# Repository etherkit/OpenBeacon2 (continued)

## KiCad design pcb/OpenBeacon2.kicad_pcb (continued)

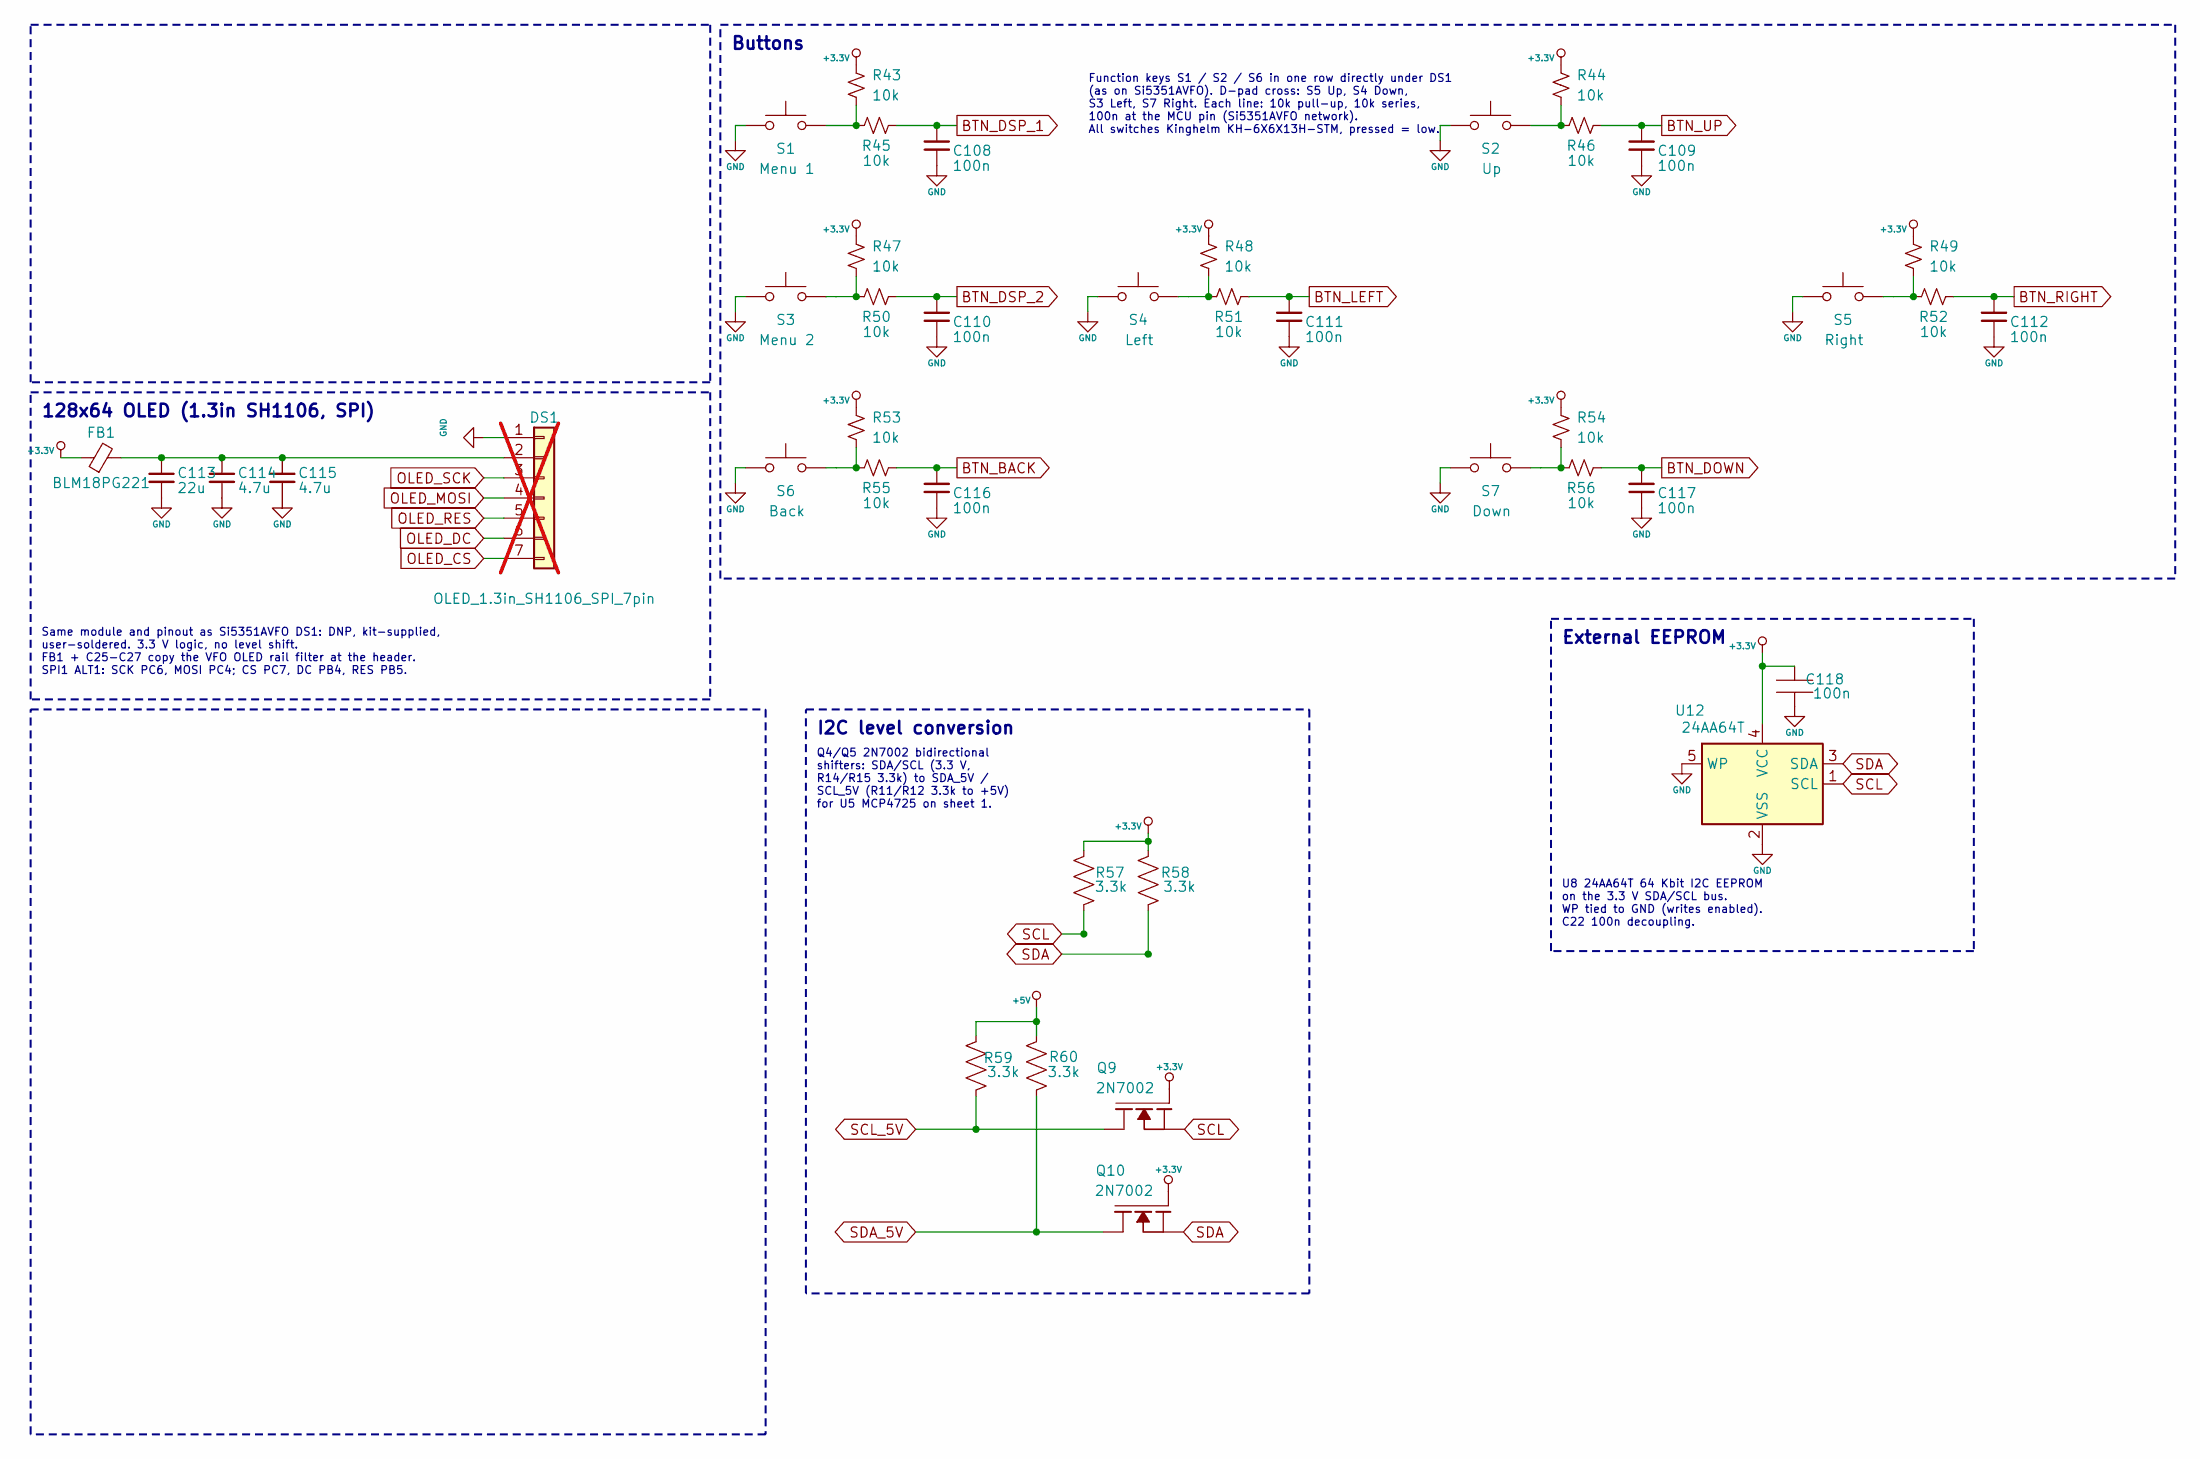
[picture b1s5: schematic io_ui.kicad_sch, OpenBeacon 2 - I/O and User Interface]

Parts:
C108, C109, C110, C111, C112, C116, C117, C118: 100n; C_0805_2012Metric; MPN CC0805KRX7R9BB104; LCSC C49678
C113: 22u; C_1206_3216Metric; MPN CL31A226KAHNNNE; LCSC C12891
C114, C115: 4.7u; C_0805_2012Metric; MPN CL21A475KAQNNNE; LCSC C1779
DS1: OLED_1.3in_SH1106_SPI_7pin; OLED_1.3in_SH1106_PinHeader_1x07_P2.54mm; MPN generic 1.3in SH1106 SPI 7-pin OLED mod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; not fitted
FB1: BLM18PG221; L_0603_1608Metric; MPN BLM18PG221SN1D; LCSC C80165
Q9, Q10: 2N7002; SOT23-2N7002; MPN 2N7002; LCSC C8545
R43, R44, R45, R46, R47, R48, R49, R50, R51, R52, R53, R54, R55, R56: 10k; R_0805_2012Metric; MPN 0805W8F1002T5E; LCSC C17414
R57, R58, R59, R60: 3.3k; R_0805_2012Metric; MPN 0805W8F3301T5E; LCSC C26010
S1: Menu 1; SW_Push_6x6mm_SMD_KH-6X6X13H-STM; MPN KH-6X6X13H-STM; LCSC C2837539
S2: Up; SW_Push_6x6mm_SMD_KH-6X6X13H-STM; MPN KH-6X6X13H-STM; LCSC C2837539
S3: Menu 2; SW_Push_6x6mm_SMD_KH-6X6X13H-STM; MPN KH-6X6X13H-STM; LCSC C2837539
S4: Left; SW_Push_6x6mm_SMD_KH-6X6X13H-STM; MPN KH-6X6X13H-STM; LCSC C2837539
S5: Right; SW_Push_6x6mm_SMD_KH-6X6X13H-STM; MPN KH-6X6X13H-STM; LCSC C2837539
S6: Back; SW_Push_6x6mm_SMD_KH-6X6X13H-STM; MPN KH-6X6X13H-STM; LCSC C2837539
S7: Down; SW_Push_6x6mm_SMD_KH-6X6X13H-STM; MPN KH-6X6X13H-STM; LCSC C2837539
U12: 24AA64T; SOT-23-5; MPN 24AA64T-I/OT; LCSC C2061092

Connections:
+3.3V: C118.1, FB1.1, Q9.2 (G), Q10.2 (G), R43.1, R44.1, R47.1, R48.1, R49.1, R53.1, R54.1, R57.1, R58.1, U12.4 (VCC); also elsewhere on the board
+5V: R59.1, R60.1; also elsewhere on the board
BTN_BACK: C116.1, R55.2; also elsewhere on the board
BTN_DOWN: C117.1, R56.2; also elsewhere on the board
BTN_DSP_1: C108.1, R45.2; also elsewhere on the board
BTN_DSP_2: C110.1, R50.2; also elsewhere on the board
BTN_LEFT: C111.1, R51.2; also elsewhere on the board
BTN_RIGHT: C112.1, R52.2; also elsewhere on the board
BTN_UP: C109.1, R46.2; also elsewhere on the board
GND: C108.2, C109.2, C110.2, C111.2, C112.2, C113.2, C114.2, C115.2, C116.2, C117.2, C118.2, DS1.1, S1.1, S2.1, S3.1, S4.1, S5.1, S6.1, S7.1, U12.2 (VSS), U12.5 (WP); also elsewhere on the board
unnamed: C113.1, C114.1, C115.1, DS1.2, FB1.2
unnamed: R43.2, R45.1, S1.2
unnamed: R44.2, R46.1, S2.2
unnamed: R47.2, R50.1, S3.2
unnamed: R48.2, R51.1, S4.2
unnamed: R49.2, R52.1, S5.2
unnamed: R53.2, R55.1, S6.2
unnamed: R54.2, R56.1, S7.2
OLED_CS: DS1.7; also elsewhere on the board
OLED_DC: DS1.6; also elsewhere on the board
OLED_MOSI: DS1.4; also elsewhere on the board
OLED_RES: DS1.5; also elsewhere on the board
OLED_SCK: DS1.3; also elsewhere on the board
SCL: Q9.1 (S), R57.2, U12.1 (SCL); also elsewhere on the board
SCL_5V: Q9.3 (D), R59.2; also elsewhere on the board
SDA: Q10.1 (S), R58.2, U12.3 (SDA); also elsewhere on the board
SDA_5V: Q10.3 (D), R60.2; also elsewhere on the board

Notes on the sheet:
128x64 OLED (1.3in SH1106, SPI)
Same module and pinout as Si5351AVFO DS1: DNP, kit-supplied, user-soldered. 3.3 V logic, no level shift. FB1 + C25-C27 copy the VFO OLED rail filter at the header. SPI1 ALT1: SCK PC6, MOSI PC4; CS PC7, DC PB4, RES PB5.
Buttons
Function keys S1 / S2 / S6 in one row directly under DS1 (as on Si5351AVFO). D-pad cross: S5 Up, S4 Down, S3 Left, S7 Right. Each line: 10k pull-up, 10k series, 100n at the MCU pin (Si5351AVFO network). All switches Kinghelm KH-6X6X13H-STM, pressed = low.
I2C level conversion
Q4/Q5 2N7002 bidirectional shifters: SDA/SCL (3.3 V, R14/R15 3.3k) to SDA_5V / SCL_5V (R11/R12 3.3k to +5V) for U5 MCP4725 on sheet 1.
External EEPROM
U8 24AA64T 64 Kbit I2C EEPROM on the 3.3 V SDA/SCL bus. WP tied to GND (writes enabled). C22 100n decoupling.

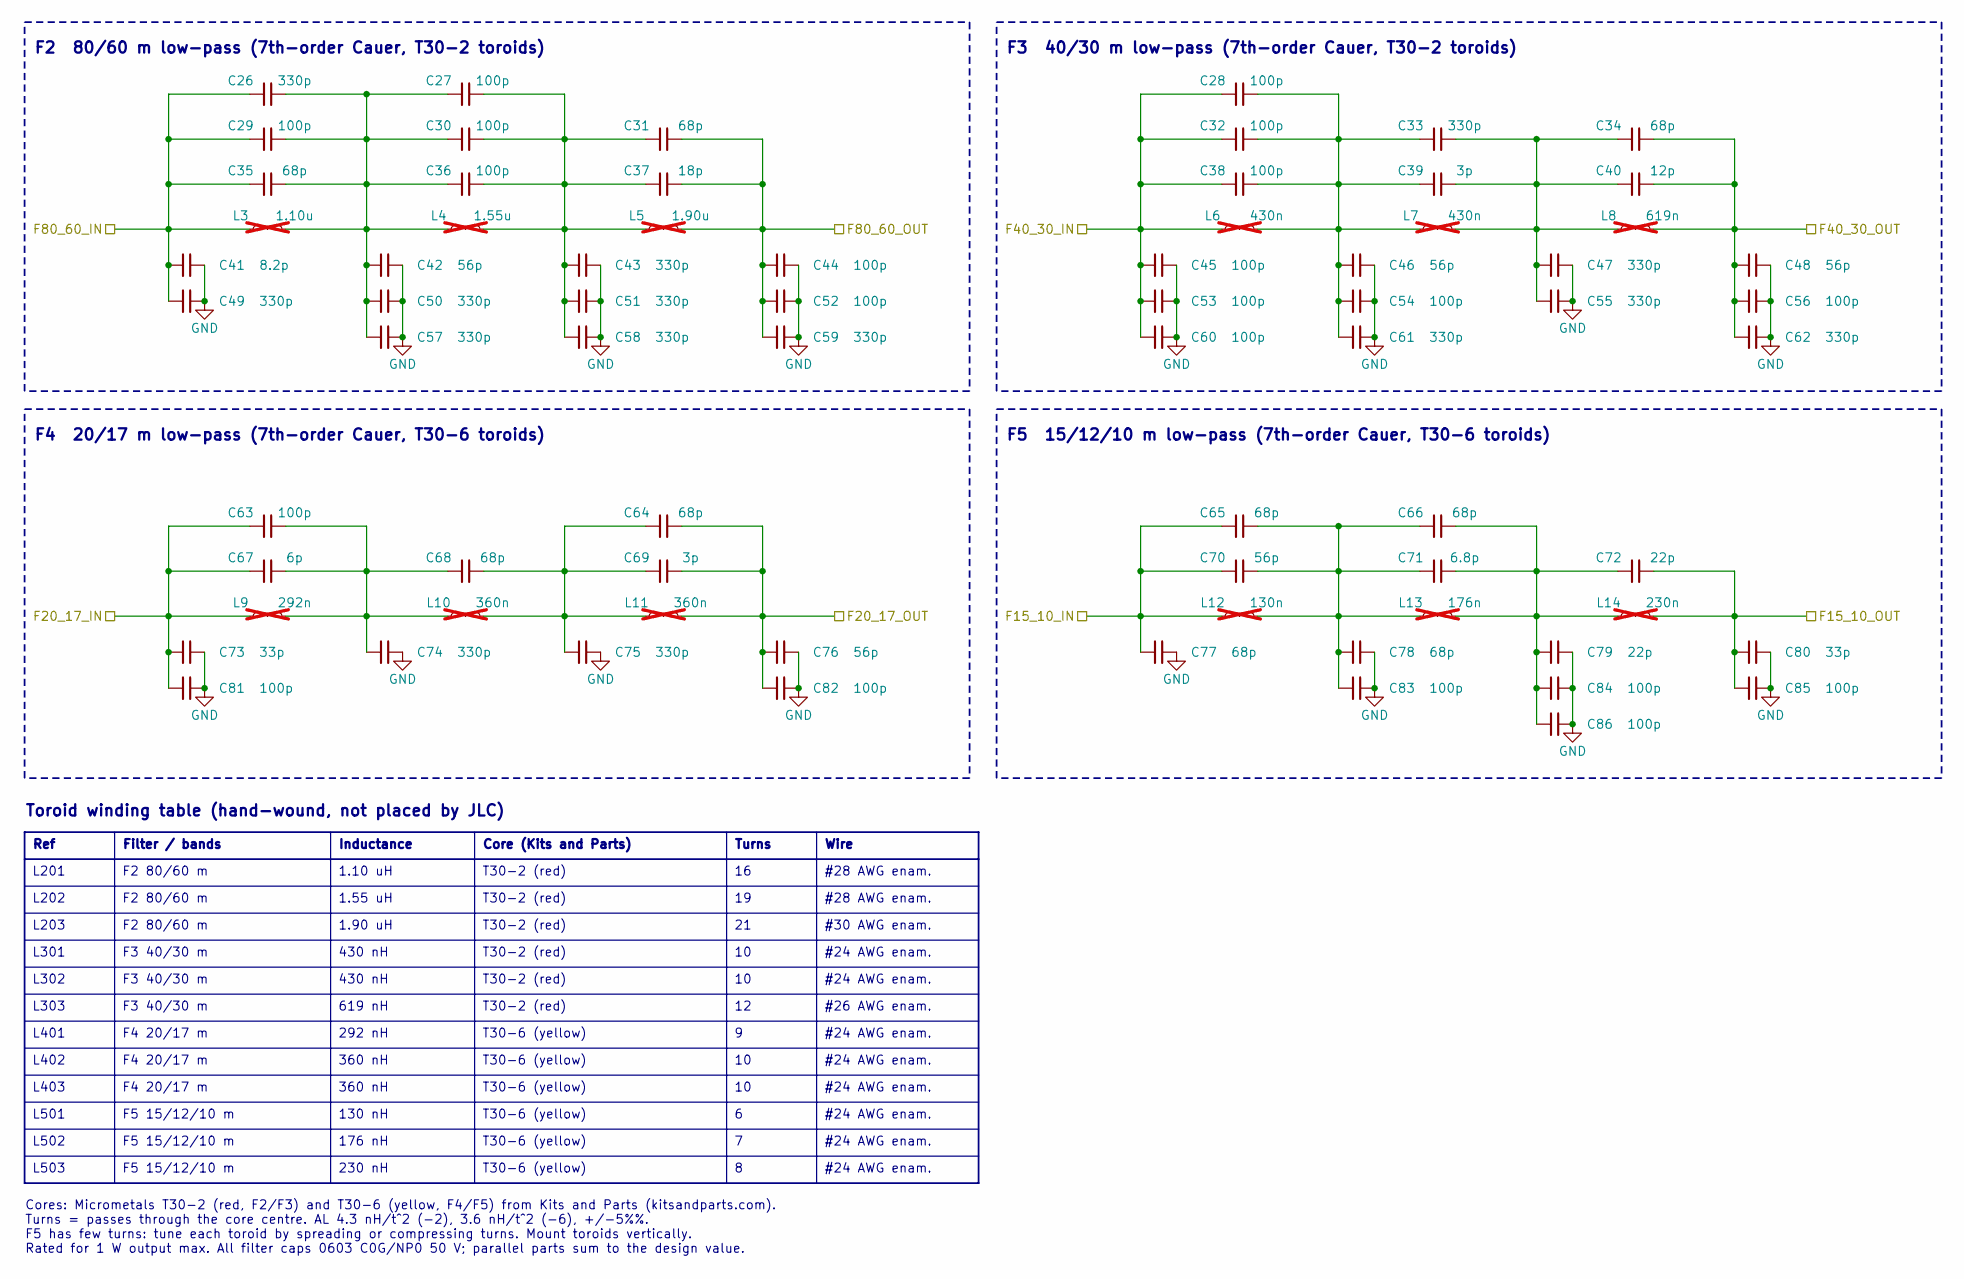
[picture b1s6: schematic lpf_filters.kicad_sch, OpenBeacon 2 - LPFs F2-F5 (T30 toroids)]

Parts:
C26: 330p; C_0603_1608Metric; MPN CC0603JRNPO0BN331; LCSC C327088
C27, C29, C30, C36: 100p; C_0603_1608Metric; MPN CC0603JRNPO0BN101; LCSC C107033
C28, C32, C38, C44, C45, C52, C53, C54, C56, C60, C63, C81, C82, C83, C84, C85, C86: 100p; C_0603_1608Metric; MPN CL10C101JB8NNNC; LCSC C14858
C31, C34, C64, C65, C66, C68, C77, C78: 68p; C_0603_1608Metric; MPN CL10C680JB8NNNC; LCSC C28262
C33, C43, C47, C49, C50, C51, C55, C57, C58, C59, C61, C62, C74, C75: 330p; C_0603_1608Metric; MPN CL10C331JB8NNNC; LCSC C1664
C35: 68p; C_0603_1608Metric; MPN CC0603JRNPO0BN680; LCSC C527065
C37: 18p; C_0603_1608Metric; MPN CL10C180JB8NNNC; LCSC C1647
C39, C69: 3p; C_0603_1608Metric; MPN 0603CG3R0C500NT; LCSC C46219
C40: 12p; C_0603_1608Metric; MPN CL10C120JB8NNNC; LCSC C38523
C41: 8.2p; C_0603_1608Metric; MPN 0603CG8R2C500NT; LCSC C1685
C42, C46, C48, C70, C76: 56p; C_0603_1608Metric; MPN CL10C560JB8NNNC; LCSC C39148
C67: 6p; C_0603_1608Metric; MPN 0603CG6R0C500NT; LCSC C37474
C71: 6.8p; C_0603_1608Metric; MPN 0603CG6R8C500NT; LCSC C1679
C72, C79: 22p; C_0603_1608Metric; MPN CL10C220JB8NNNC; LCSC C1653
C73, C80: 33p; C_0603_1608Metric; MPN CL10C330JB8NNNC; LCSC C1663
L3: 1.10u; L_Toroid_Vertical_L10.0mm_W5.0mm_P5.08mm; MPN T30-2; not fitted
L4: 1.55u; L_Toroid_Vertical_L10.0mm_W5.0mm_P5.08mm; MPN T30-2; not fitted
L5: 1.90u; L_Toroid_Vertical_L10.0mm_W5.0mm_P5.08mm; MPN T30-2; not fitted
L6, L7: 430n; L_Toroid_Vertical_L10.0mm_W5.0mm_P5.08mm; MPN T30-2; not fitted
L8: 619n; L_Toroid_Vertical_L10.0mm_W5.0mm_P5.08mm; MPN T30-2; not fitted
L9: 292n; L_Toroid_Vertical_L10.0mm_W5.0mm_P5.08mm; MPN T30-6; not fitted
L10, L11: 360n; L_Toroid_Vertical_L10.0mm_W5.0mm_P5.08mm; MPN T30-6; not fitted
L12: 130n; L_Toroid_Vertical_L10.0mm_W5.0mm_P5.08mm; MPN T30-6; not fitted
L13: 176n; L_Toroid_Vertical_L10.0mm_W5.0mm_P5.08mm; MPN T30-6; not fitted
L14: 230n; L_Toroid_Vertical_L10.0mm_W5.0mm_P5.08mm; MPN T30-6; not fitted

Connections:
/Filter Bank/F15_10_IN: C65.1, C70.1, C77.1, L12.1; also elsewhere on the board
/Filter Bank/F15_10_OUT: C72.2, C80.1, C85.1, L14.2; also elsewhere on the board
/Filter Bank/F20_17_IN: C63.1, C67.1, C73.1, C81.1, L9.1; also elsewhere on the board
/Filter Bank/F20_17_OUT: C64.2, C69.2, C76.1, C82.1, L11.2; also elsewhere on the board
/Filter Bank/F40_30_IN: C28.1, C32.1, C38.1, C45.1, C53.1, C60.1, L6.1; also elsewhere on the board
/Filter Bank/F40_30_OUT: C34.2, C40.2, C48.1, C56.1, C62.1, L8.2; also elsewhere on the board
/Filter Bank/F80_60_IN: C26.1, C29.1, C35.1, C41.1, C49.1, L3.1; also elsewhere on the board
/Filter Bank/F80_60_OUT: C31.2, C37.2, C44.1, C52.1, C59.1, L5.2; also elsewhere on the board
GND: C41.2, C42.2, C43.2, C44.2, C45.2, C46.2, C47.2, C48.2, C49.2, C50.2, C51.2, C52.2, C53.2, C54.2, C55.2, C56.2, C57.2, C58.2, C59.2, C60.2, C61.2, C62.2, C73.2, C74.2, C75.2, C76.2, C77.2, C78.2, C79.2, C80.2, C81.2, C82.2, C83.2, C84.2, C85.2, C86.2; also elsewhere on the board
unnamed: C26.2, C27.1, C29.2, C30.1, C35.2, C36.1, C42.1, C50.1, C57.1, L3.2, L4.1
unnamed: C27.2, C30.2, C31.1, C36.2, C37.1, C43.1, C51.1, C58.1, L4.2, L5.1
unnamed: C28.2, C32.2, C33.1, C38.2, C39.1, C46.1, C54.1, C61.1, L6.2, L7.1
unnamed: C33.2, C34.1, C39.2, C40.1, C47.1, C55.1, L7.2, L8.1
unnamed: C63.2, C67.2, C68.1, C74.1, L9.2, L10.1
unnamed: C64.1, C68.2, C69.1, C75.1, L10.2, L11.1
unnamed: C65.2, C66.1, C70.2, C71.1, C78.1, C83.1, L12.2, L13.1
unnamed: C66.2, C71.2, C72.1, C79.1, C84.1, C86.1, L13.2, L14.1

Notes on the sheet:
F2 80/60 m low-pass (7th-order Cauer, T30-2 toroids)
F3 40/30 m low-pass (7th-order Cauer, T30-2 toroids)
F4 20/17 m low-pass (7th-order Cauer, T30-6 toroids)
F5 15/12/10 m low-pass (7th-order Cauer, T30-6 toroids)
Toroid winding table (hand-wound, not placed by JLC)
Ref
Filter / bands
Inductance
Core (Kits and Parts)
Turns
Wire
L201
F2 80/60 m
1.10 uH
T30-2 (red)
#28 AWG enam.
L202
1.55 uH
L203
1.90 uH
#30 AWG enam.
L301
F3 40/30 m
430 nH
#24 AWG enam.
L302
L303
619 nH
#26 AWG enam.
L401
F4 20/17 m
292 nH
T30-6 (yellow)
L402
360 nH
L403
L501
F5 15/12/10 m
130 nH
L502

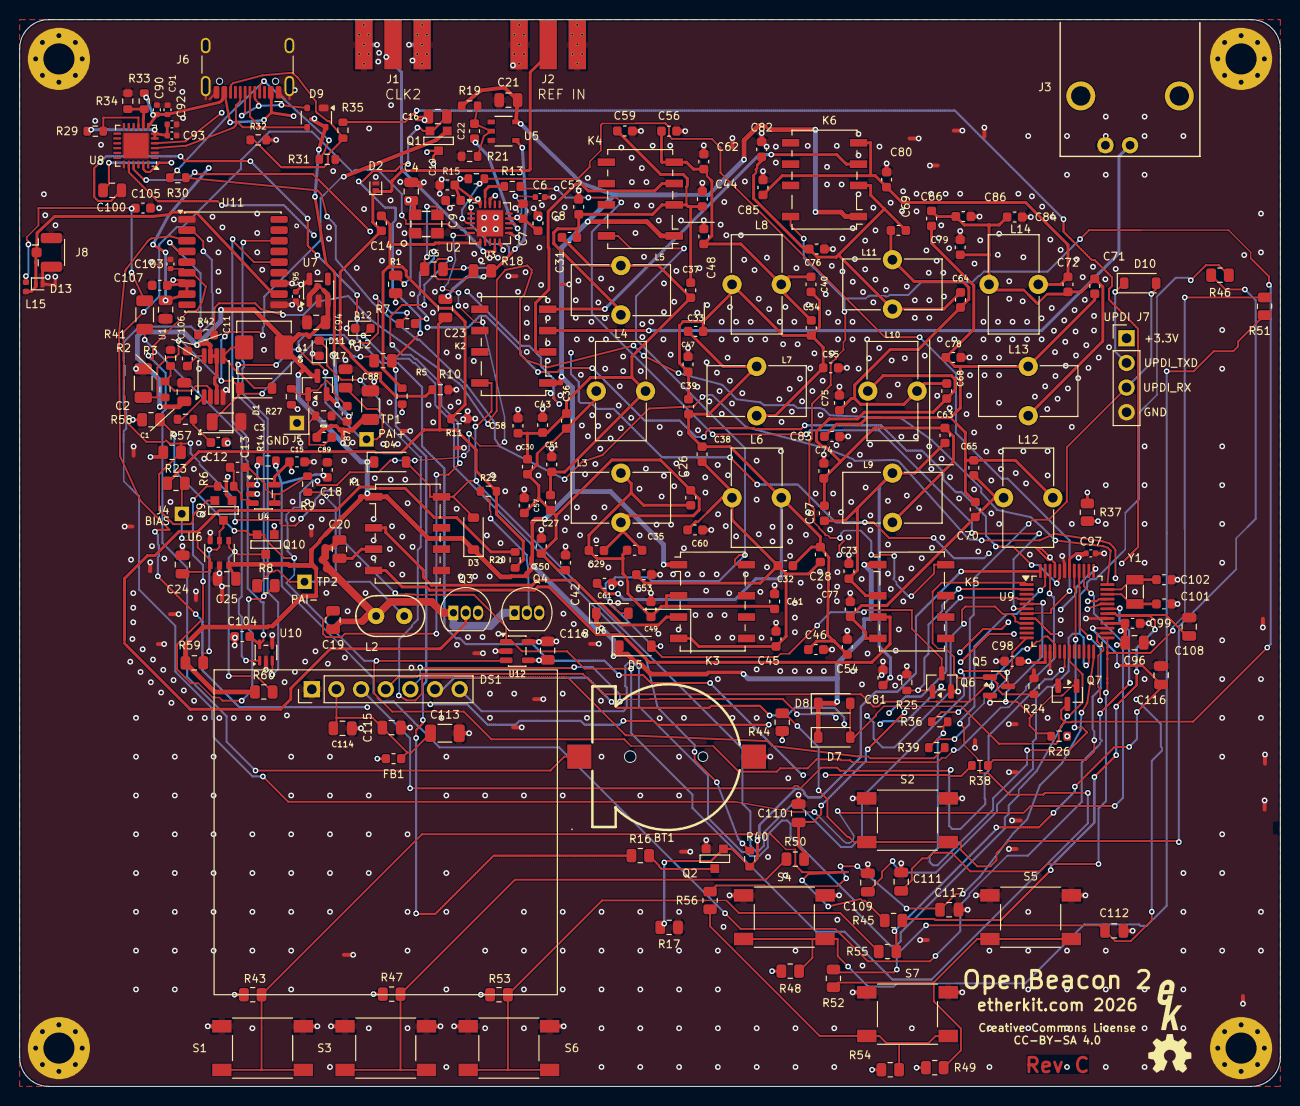
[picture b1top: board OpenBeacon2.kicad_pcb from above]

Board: 4 copper layers, 130.0 x 110.0 mm, 261 parts (0 on the bottom side), 123 nets.

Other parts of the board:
H1, H2, H3, H4: MountingHole_M3; MountingHole_3.2mm_M3_Pad_Via
LOGO1: LOGO; EtherkitLogoSmall
LOGO2: LOGO; OSHWLogo4mm

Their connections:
GND: H1.1, H2.1, H3.1, H4.1; also elsewhere on the board

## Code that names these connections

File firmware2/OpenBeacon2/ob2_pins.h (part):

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 *
 * Transcribed from the firmware spec draft 3.5 (approved), section 2.1,
 * with the section 2.2 power-rework net changes applied. DxCore numbers are
 * the 48pin-standard map (PA0 = 0 ... PF5 = 39). This header includes no
 * Arduino headers, so host tests can compile it.
 *
 * POWER REWORK HARDWARE IS NOT COMMITTED IN THIS REPOSITORY.
 * origin/pcb-layout commit 88e9a62 still has PB1 no-connect and PE1-PE3 on
 * header J5 (labels D31_A9_PE1, D32_A10_PE2, D33_A11_PE3). Spec section 2.2
 * (decision D17) supersedes those four nets. This header follows section 2.2.
 * It is not evidence that the rework schematic has landed.
 *
 * Spec section 2.1 leaves the DxCore column blank for PF0, PF1, RESET/PF6,
 * and UPDI. DxCore still numbers PIN_PF0 = 34, PIN_PF1 = 35, and PIN_PF6 = 40.
 * Those pins are not given firmware GPIO constants here (crystal and reset).
 *
 * The three J5 spares are one row in the spec ("PD0-PD2 / J5"). They are
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
constexpr char OB2_POWER_REWORK_NOTE[] =
    "Power rework (D17) is not committed in this repository. "
    "PB1 BAND_C, PE1 TX_ISENSE, PE2 CC1_SENSE, and PE3 CC2_SENSE follow "
    "spec section 2.2, which supersedes pcb-layout 88e9a62 "
    "(PB1 NC, PE1-PE3 on J5).";

constexpr uint8_t OB2_PIN_REWORK = 1u << 0;
constexpr uint8_t OB2_PIN_OUT = 1u << 1;
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constexpr uint8_t OB2_PIN_NO_GPIO = 1u << 6;

/* Firmware GPIO numbers. Spec section 2.1 "DxCore" column. */
constexpr uint8_t OB2_BAND_A = 5;      /* PA5 */
constexpr uint8_t OB2_BAND_B = 6;      /* PA6 */
constexpr uint8_t OB2_J4_PA7 = 7;      /* PA7, spare J4.1 */
constexpr uint8_t OB2_GPS_RXD = 8;     /* PB0, USART3 TX to the GPS */
constexpr uint8_t OB2_BAND_C = 9;      /* PB1, rework */
constexpr uint8_t OB2_CAL_CLK = 10;    /* PB2, Si5351C CLK4 */
constexpr uint8_t OB2_SI_INTR = 11;    /* PB3 */
constexpr uint8_t OB2_OLED_DC = 12;    /* PB4 */
constexpr uint8_t OB2_OLED_RES = 13;   /* PB5 */
constexpr uint8_t OB2_UART_TX = 14;    /* PC0, USART1 TX, J10 */
constexpr uint8_t OB2_UART_RX = 15;    /* PC1, USART1 RX, J10 */
constexpr uint8_t OB2_SYNC_LED = 16;   /* PC2 */
constexpr uint8_t OB2_J4_PC3 = 17;     /* PC3, spare J4.3 */
constexpr uint8_t OB2_OLED_MOSI = 18;  /* PC4, SPI1 ALT1 */
constexpr uint8_t OB2_J4_PC5 = 19;     /* PC5, spare J4.5, SPI1 ALT1 MISO */
constexpr uint8_t OB2_OLED_SCK = 20;   /* PC6, SPI1 ALT1 */
constexpr uint8_t OB2_OLED_CS = 21;    /* PC7, SPI1 ALT1 SS as GPIO */
constexpr uint8_t OB2_J5_PD0 = 22;     /* PD0, spare ADC A0 */
constexpr uint8_t OB2_J5_PD1 = 23;     /* PD1, spare ADC A1 */
constexpr uint8_t OB2_J5_PD2 = 24;     /* PD2, spare ADC A2 */
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constexpr uint8_t OB2_BTN_DOWN = 26;
constexpr uint8_t OB2_BTN_LEFT = 27;
constexpr uint8_t OB2_BTN_RIGHT = 28;
constexpr uint8_t OB2_BTN_BACK = 29;   /* PD7. Do not select VREFA. */
constexpr uint8_t OB2_BTN_DSP_1 = 30;  /* PE0 */
constexpr uint8_t OB2_TX_ISENSE = 31;  /* PE1, AIN9, rework */
constexpr uint8_t OB2_CC1_SENSE = 32;  /* PE2, AIN10, rework */
constexpr uint8_t OB2_CC2_SENSE = 33;  /* PE3, AIN11, rework */
constexpr uint8_t OB2_GPS_PPS = 36;    /* PF2 */
constexpr uint8_t OB2_BTN_DSP_2 = 37;  /* PF3 */
constexpr uint8_t OB2_J4_PF4 = 38;     /* PF4, spare J4.7 */
constexpr uint8_t OB2_GPS_TXD = 39;    /* PF5, USART2 RX ALT1 */
constexpr uint8_t OB2_MCU_TX = 0;      /* PA0, USART0 TX to the CP2102N */
constexpr uint8_t OB2_MCU_RX = 1;      /* PA1, USART0 RX */
constexpr uint8_t OB2_SDA = 2;         /* PA2, TWI0 */
constexpr uint8_t OB2_SCL = 3;         /* PA3, TWI0 */
constexpr uint8_t OB2_TX = 4;          /* PA4, 12 V PA supply and TX LED */

constexpr int8_t OB2_AIN_J5_PD0 = 0;
constexpr int8_t OB2_AIN_J5_PD1 = 1;
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constexpr int8_t OB2_AIN_CC2_SENSE = 11;

/*
 * USART2 on ALT1, RX only: GPS TXD -> PF5. ALT1 TX is PF4 (J4.7) and must
 * stay a GPIO. Default USART2 would sit on the 32 kHz crystal (PF0/PF1).
 * USART3 default, TX only: MCU -> GPS RXD on PB0. RX is PB1 (BAND_C);
 * RXEN must stay off or it takes the relay pin.
 */
constexpr uint8_t OB2_USART2_RX = OB2_GPS_TXD;
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constexpr uint8_t OB2_USART3_RX_DISABLED = OB2_BAND_C;
constexpr uint8_t OB2_USART3_PORTMUX_DEFAULT = 0;

/* Si5351C CLK4 calibration input on PB2. */
constexpr uint8_t OB2_CLK4_CAL = OB2_CAL_CLK;

/*
 * Display is SPI1 ALT1 (MOSI PC4, MISO PC5, SCK PC6, SS PC7 as GPIO).
 * Do not start SPI0: its default pins are PA4-PA7 (TX, BAND_A, BAND_B, J4.1).
 * Do not start SPI1 on the default mux: MOSI/SCK/SS land on PC0/PC2/PA3
 * (UART_TX, SYNC_LED, SCL). PC5 is forced to an input while SPI1 is master.
 */
constexpr uint8_t OB2_SPI1_MOSI = OB2_OLED_MOSI;
constexpr uint8_t OB2_SPI1_MISO = OB2_J4_PC5;
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};

static constexpr Ob2Pin OB2_PINS[] = {
    {1, 'A', 5, 5, -1, "BAND_A", "GPIO out to Q6 (K1/K4)", OB2_PIN_OUT},
    {2, 'A', 6, 6, -1, "BAND_B",
     "GPIO out to Q7 (K2/K5). Spec section 2.1 still says Q7 drives K2/K3/K5/K6; "
     "section 2.2 assigns K3/K6 to BAND_C.",
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     "USART3 TxD (default) to GPS RXD. USART3 RXEN stays off.", 0},
    {5, 'B', 1, 9, -1, "BAND_C",
     "GPIO out to Q9 (K3/K6), low at reset, R91 22k pull-down. "
     "USART3 RX pin: RXEN stays off. Rework net; 88e9a62 leaves PB1 unconnected.",
     OB2_PIN_OUT | OB2_PIN_REWORK},
    {6, 'B', 2, 10, -1, "CAL_CLK", "Si5351C CLK4 input. EVSYS to TCB0 count.", OB2_PIN_IN},
    {7, 'B', 3, 11, -1, "SI_INTR", "Si5351C INTR (LOS/LOL), input and pin interrupt.", OB2_PIN_IN},
    {8, 'B', 4, 12, -1, "OLED_DC", "GPIO out, SH1106 D/C.", OB2_PIN_OUT},
    {9, 'B', 5, 13, -1, "OLED_RES", "GPIO out, SH1106 reset.", OB2_PIN_OUT},
    {10, 'C', 0, 14, -1, "UART_TX", "USART1 TxD to J10.", 0},
    {11, 'C', 1, 15, -1, "UART_RX", "USART1 RxD from J10.", 0},
    {12, 'C', 2, 16, -1, "SYNC_LED", "GPIO out, SYNC LED D11.", OB2_PIN_OUT},
    {13, 'C', 3, 17, -1, "J4.3", "Spare header J4.3. Committed label D17_PC3.", OB2_PIN_SPARE},
    {14, 0, -1, -1, -1, "VDD", "Power. Package pins 14 and 42.", OB2_PIN_POWER | OB2_PIN_NO_GPIO},
    {15, 0, -1, -1, -1, "GND", "Ground. Package pins 15, 29, and 43.", OB2_PIN_POWER | OB2_PIN_NO_GPIO},
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     "Committed label D19_PC5.",
     OB2_PIN_SPARE},
    {18, 'C', 6, 20, -1, "OLED_SCK", "SPI1 ALT1 SCK.", 0},
    {19, 'C', 7, 21, -1, "OLED_CS", "SPI1 ALT1 SS, driven as GPIO chip select (must be an output).", OB2_PIN_OUT},
    {20, 'D', 0, 22, 0, "J5",
     "Spare header J5, ADC A0 / AIN0. Committed label D22_A0_PD0. Stays on J5 after the rework.",
     OB2_PIN_SPARE | OB2_PIN_ADC},
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    {22, 'D', 2, 24, 2, "J5",
     "Spare header J5, ADC A2 / AIN2. Committed label D24_A2_PD2. Stays on J5 after the rework.",
     OB2_PIN_SPARE | OB2_PIN_ADC},
    {23, 'D', 3, 25, -1, "BTN_UP", "Input, pressed = low.", OB2_PIN_IN},
    {24, 'D', 4, 26, -1, "BTN_DOWN", "Input, pressed = low.", OB2_PIN_IN},
    {25, 'D', 5, 27, -1, "BTN_LEFT", "Input, pressed = low.", OB2_PIN_IN},
    {26, 'D', 6, 28, -1, "BTN_RIGHT", "Input, pressed = low.", OB2_PIN_IN},
    {27, 'D', 7, 29, -1, "BTN_BACK",
     "Input, pressed = low. PD7 is VREFA: do not select VREFA as the ADC reference.", OB2_PIN_IN},
    {28, 0, -1, -1, -1, "AVDD", "Analog supply. Package pin 28.", OB2_PIN_POWER | OB2_PIN_NO_GPIO},
    {29, 0, -1, -1, -1, "GND", "Ground. Package pins 15, 29, and 43.", OB2_PIN_POWER | OB2_PIN_NO_GPIO},
    {30, 'E', 0, 30, -1, "BTN_DSP_1", "Input, pressed = low. S1 Menu1.", OB2_PIN_IN},
    {31, 'E', 1, 31, 9, "TX_ISENSE",
     "ADC AIN9, PA current. Rework net; 88e9a62 label is D31_A9_PE1 on J5.",
     OB2_PIN_ADC | OB2_PIN_REWORK},
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     "ADC AIN11, USB-C CC2. Rework net; 88e9a62 label is D33_A11_PE3 on J5.",
     OB2_PIN_ADC | OB2_PIN_REWORK},
    {34, 'F', 0, -1, -1, "Y1",
     "XOSC32K TOSC1. Not a firmware GPIO. Spec DxCore column is blank; DxCore PIN_PF0 is 34.",
     OB2_PIN_NO_GPIO},
    {35, 'F', 1, -1, -1, "Y1",
     "XOSC32K TOSC2. Not a firmware GPIO. Spec DxCore column is blank; DxCore PIN_PF1 is 35.",
     OB2_PIN_NO_GPIO},
    {36, 'F', 2, 36, -1, "GPS_PPS", "GPS timepulse. EVSYS capture.", OB2_PIN_IN},
    {37, 'F', 3, 37, -1, "BTN_DSP_2", "Input, pressed = low. S2 Menu2.", OB2_PIN_IN},
    {38, 'F', 4, 38, -1, "J4.7",
     "Spare header J4.7. Must not become USART2 TxD. Committed label D38_A20_PF4.",
     OB2_PIN_SPARE},
    {39, 'F', 5, 39, -1, "GPS_TXD",
     "USART2 RxD, PORTMUX ALT1, RX only. GPS TXD into the MCU. Do not enable TXEN.", 0},
    {40, 'F', 6, -1, -1, "RESET",
     "DTR auto-reset through C37/R36. Not a firmware GPIO. Spec DxCore column is blank; "
     "DxCore PIN_PF6 is 40.",
     OB2_PIN_NO_GPIO},
    {41, 0, -1, -1, -1, "J13", "UPDI programming header.", OB2_PIN_NO_GPIO},
    {42, 0, -1, -1, -1, "VDD", "Power. Package pins 14 and 42.", OB2_PIN_POWER | OB2_PIN_NO_GPIO},
    {43, 0, -1, -1, -1, "GND", "Ground. Package pins 15, 29, and 43.", OB2_PIN_POWER | OB2_PIN_NO_GPIO},
    {44, 'A', 0, 0, -1, "MCU_TX", "USART0 TxD to CP2102N RXD. Host protocol.", 0},
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
static_assert(ob2_pins_unique(), "U9 pin table has a duplicate or the wrong count");
static_assert(ob2_rework_count() == 4, "spec section 2.2 changes four pins");
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
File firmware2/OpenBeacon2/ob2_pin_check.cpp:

/*
 * Compile-time cross-check of ob2_pins.h against the DxCore 48-pin map.
 * A failure here means DxCore's numbers moved relative to spec section 2.1.
 * Do not edit the spec numbers in the header to silence an assert; record
 * the mismatch.
 */

#include <Arduino.h>

#include "ob2_pins.h"

static_assert(OB2_BAND_A == PIN_PA5, "PA5");
static_assert(OB2_BAND_B == PIN_PA6, "PA6");
static_assert(OB2_J4_PA7 == PIN_PA7, "PA7");
static_assert(OB2_GPS_RXD == PIN_PB0, "PB0");
static_assert(OB2_BAND_C == PIN_PB1, "PB1");
static_assert(OB2_CAL_CLK == PIN_PB2, "PB2");
static_assert(OB2_SI_INTR == PIN_PB3, "PB3");
static_assert(OB2_OLED_DC == PIN_PB4, "PB4");
static_assert(OB2_OLED_RES == PIN_PB5, "PB5");
static_assert(OB2_UART_TX == PIN_PC0, "PC0");
static_assert(OB2_UART_RX == PIN_PC1, "PC1");
static_assert(OB2_SYNC_LED == PIN_PC2, "PC2");
static_assert(OB2_J4_PC3 == PIN_PC3, "PC3");
static_assert(OB2_OLED_MOSI == PIN_PC4, "PC4");
static_assert(OB2_J4_PC5 == PIN_PC5, "PC5");
static_assert(OB2_OLED_SCK == PIN_PC6, "PC6");
static_assert(OB2_OLED_CS == PIN_PC7, "PC7");
static_assert(OB2_J5_PD0 == PIN_PD0, "PD0");
static_assert(OB2_J5_PD1 == PIN_PD1, "PD1");
static_assert(OB2_J5_PD2 == PIN_PD2, "PD2");
static_assert(OB2_BTN_UP == PIN_PD3, "PD3");
static_assert(OB2_BTN_DOWN == PIN_PD4, "PD4");
static_assert(OB2_BTN_LEFT == PIN_PD5, "PD5");
static_assert(OB2_BTN_RIGHT == PIN_PD6, "PD6");
static_assert(OB2_BTN_BACK == PIN_PD7, "PD7");
static_assert(OB2_BTN_DSP_1 == PIN_PE0, "PE0");
static_assert(OB2_TX_ISENSE == PIN_PE1, "PE1");
static_assert(OB2_CC1_SENSE == PIN_PE2, "PE2");
static_assert(OB2_CC2_SENSE == PIN_PE3, "PE3");
static_assert(OB2_GPS_PPS == PIN_PF2, "PF2");
static_assert(OB2_BTN_DSP_2 == PIN_PF3, "PF3");
static_assert(OB2_J4_PF4 == PIN_PF4, "PF4");
static_assert(OB2_GPS_TXD == PIN_PF5, "PF5");
static_assert(OB2_MCU_TX == PIN_PA0, "PA0");
static_assert(OB2_MCU_RX == PIN_PA1, "PA1");
static_assert(OB2_SDA == PIN_PA2, "PA2");
static_assert(OB2_SCL == PIN_PA3, "PA3");
static_assert(OB2_TX == PIN_PA4, "PA4");

static_assert(PIN_A0 == PIN_PD0, "A0");
static_assert(PIN_A1 == PIN_PD1, "A1");
static_assert(PIN_A2 == PIN_PD2, "A2");
static_assert(PIN_A9 == PIN_PE1, "AIN9");
static_assert(PIN_A10 == PIN_PE2, "AIN10");
static_assert(PIN_A11 == PIN_PE3, "AIN11");

static_assert(PIN_HWSERIAL0_TX == PIN_PA0, "USART0 TX");
static_assert(PIN_HWSERIAL0_RX == PIN_PA1, "USART0 RX");
static_assert(PIN_HWSERIAL1_TX == PIN_PC0, "USART1 TX");
static_assert(PIN_HWSERIAL1_RX == PIN_PC1, "USART1 RX");
static_assert(PIN_HWSERIAL2_RX_PINSWAP_1 == PIN_PF5, "USART2 ALT1 RX");
static_assert(PIN_HWSERIAL2_TX_PINSWAP_1 == PIN_PF4, "USART2 ALT1 TX is J4.7");
static_assert(PIN_HWSERIAL2_TX == PIN_PF0, "USART2 default TX is the crystal");
static_assert(PIN_HWSERIAL2_RX == PIN_PF1, "USART2 default RX is the crystal");
static_assert(PIN_HWSERIAL3_TX == PIN_PB0, "USART3 TX");
static_assert(PIN_HWSERIAL3_RX == PIN_PB1, "USART3 RX is BAND_C");

static_assert(PIN_SPI1_MOSI_PINSWAP_1 == PIN_PC4, "SPI1 ALT1 MOSI");
static_assert(PIN_SPI1_MISO_PINSWAP_1 == PIN_PC5, "SPI1 ALT1 MISO");
static_assert(PIN_SPI1_SCK_PINSWAP_1 == PIN_PC6, "SPI1 ALT1 SCK");
static_assert(PIN_SPI1_SS_PINSWAP_1 == PIN_PC7, "SPI1 ALT1 SS");
static_assert(PIN_WIRE_SDA == PIN_PA2, "TWI0 SDA");
static_assert(PIN_WIRE_SCL == PIN_PA3, "TWI0 SCL");

/*
 * Spec section 2.1 leaves these DxCore numbers blank. The macros still exist.
 * There is no OB2_* GPIO constant for them.
 */
static_assert(PIN_PF0 == 34, "crystal pin PF0");
static_assert(PIN_PF1 == 35, "crystal pin PF1");
static_assert(PIN_PF6 == 40, "RESET pin PF6");

/*
 * DxCore's default LED_BUILTIN is PA7, the J4.1 spare, not SYNC_LED (PC2)
 * and not the TX LED (the PA4 supply net). The stub does not use it.
 */
static_assert(LED_BUILTIN == PIN_PA7, "LED_BUILTIN is the J4 spare");

/*
 * pins_arduino.h comments on digital_pin_to_bit_mask[] call PF2-PF5
 * AIN12-AIN15. PIN_A18..PIN_A21 in that same file are PF2-PF5, and the
 * datasheet calls those AIN18-AIN21. Spec section 2.1 only names AIN9/10/11.
 * The asserts below lock the macros. Do not copy the AIN12-AIN15 comments.
 */
static_assert(PIN_A18 == PIN_PF2, "PF2 analog macro is A18, not A12");
static_assert(PIN_A19 == PIN_PF3, "PF3 analog macro is A19");
static_assert(PIN_A20 == PIN_PF4, "PF4 analog macro is A20");
static_assert(PIN_A21 == PIN_PF5, "PF5 analog macro is A21");

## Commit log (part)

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2012-12-13 Add Manhattan layout diagram
2012-12-16 Add firmware
2017-12-03 New OpenBeacon Mini for 2017
2017-12-03 Add I2C level conversion
2018-01-30 Add firmware to repo
2018-04-28 New firmware and time sync software
2018-05-07 Get TX timing correct
2018-05-09 Add TX lock and TX enable
2018-05-11 Add the other MFSK modes
2018-05-12 Fix logic for reading band module
2018-05-14 Add support for QRSS and DFCW
2018-05-29 Update client sync program with cli argument support
2018-05-29 Updated quick start, timesync.py handles args
2018-05-30 Update timesync.py to ensure Win compatibility
2018-05-30 Tweak Quick Start
2018-05-30 Fix timesync.py to capture appropriate exit keys
2018-06-01 Some ADC fixes
2018-06-02 Fix directory
2018-06-05 Add mech dwgs for acrylic
2018-06-09 refining timesync.py
2018-06-09 Fix timesync.py so that terminal echo works after exit
2018-06-09 More tweaks to timesync.py
2018-08-30 Fix band ID algorithm to lock TX except when module removed
2018-08-31 Fix string settings menu adjustments
2018-09-06 Add Ins and Del menu edit options
2018-09-10 Tweak client to avoid hang on time sync
2018-09-11 Add sleep to main loop so we do not eat up CPU resources
2018-09-11 Implement PA bias, uint setting routine
2018-09-16 Add buffer selection and edit menu
2018-09-18 Add csv BOM
2018-11-18 Reimplement config storage, implement flash NVM
2018-11-19 Add CWID
2018-11-19 Fix missing holes in acrylic'
2018-11-21 Add initial support for external EEPROM for config
2018-11-21 Various bug fixes to config and mode setting logic
2018-11-22 Add config reset, welcome screen
2018-11-27 Fix wrong schematic in Documentation folder
2018-11-28 Initial schematic to Rev B
2018-11-28 Add debounce caps to buttons
2018-12-09 Initial sl support for FT8
2018-12-10 Firmware support for Rev A and Rev B boards
2018-12-10 Fix various problems with the MFSK buffer being generated correctly
2018-12-10 Fix TX timing error
2019-03-18 Add protocol document and test script
2019-03-18 Update serial protocol doc
2019-03-30 Update firmware and client for new serial comms protocol
2019-05-09 Major sync program update, remote control implemented
2019-05-09 Build standalone exe for Linux with pyinstaller
2019-05-09 Add Windows build of obmsync
2019-05-09 Cleanup venv
2019-05-10 Filename changes
2019-05-10 Add linux-arm build for Raspberry Pi
2019-05-12 Make sure timesync happens on the actual second
2019-05-12 Linux ARM build of obmsync
2019-05-14 Build obmsync for Win
2019-09-17 Change name to OpenBeacon 2
2019-09-17 Update sync program for linux-x86
2019-09-17 Fix ob2sync genrator scripts
2019-09-18 Generate ob2sync for Windows
2019-09-18 Cleanup ob2sync mess
2019-09-18 Generate ob2sync for linux-arm
2019-09-19 Fix fw where freq would show as 0 during startup
2019-09-19 Add basic screensaver
2019-09-20 Refine screen saver
2019-10-07 Fix ArduinoJSON RAM corruption, tweak client
2019-10-11 Add TX progress to screen saver
2019-10-13 Refine screen saver TX progress
2019-10-13 Major source code reorganization
2019-10-14 Add random TX frequency
2019-10-17 Add rnd_tx support to serial, add example Python script
2019-11-01 Add WSPR multiband TX script
2019-12-21 Finish Quick Start, update Linux x86 client
2019-12-21 update gitignore
2019-12-21 Update Linux ARM client
2019-12-21 Update Windows client
2019-12-23 Add get rnd_tx to firmware
2019-12-26 Fix dfcw_offset from doing nothing
2019-12-27 Add multi_dfcw_wspr.py script
2019-12-27 Increase transmit guard band to 30 Hz
2019-12-27 Add single_dfcw_wspr.py script
2019-12-30 Fix TX timing lag, buffer overflow in display code
2019-12-30 Fix scripts using 100% CPU
2020-08-24 Fix ArduinoJSON error in firmware
2020-08-24 Fix ArduinoJSON long long error, update linux-x86 client
2020-08-25 Add MacOS client build
2020-08-25 Fix bug in tx disable in firmware
